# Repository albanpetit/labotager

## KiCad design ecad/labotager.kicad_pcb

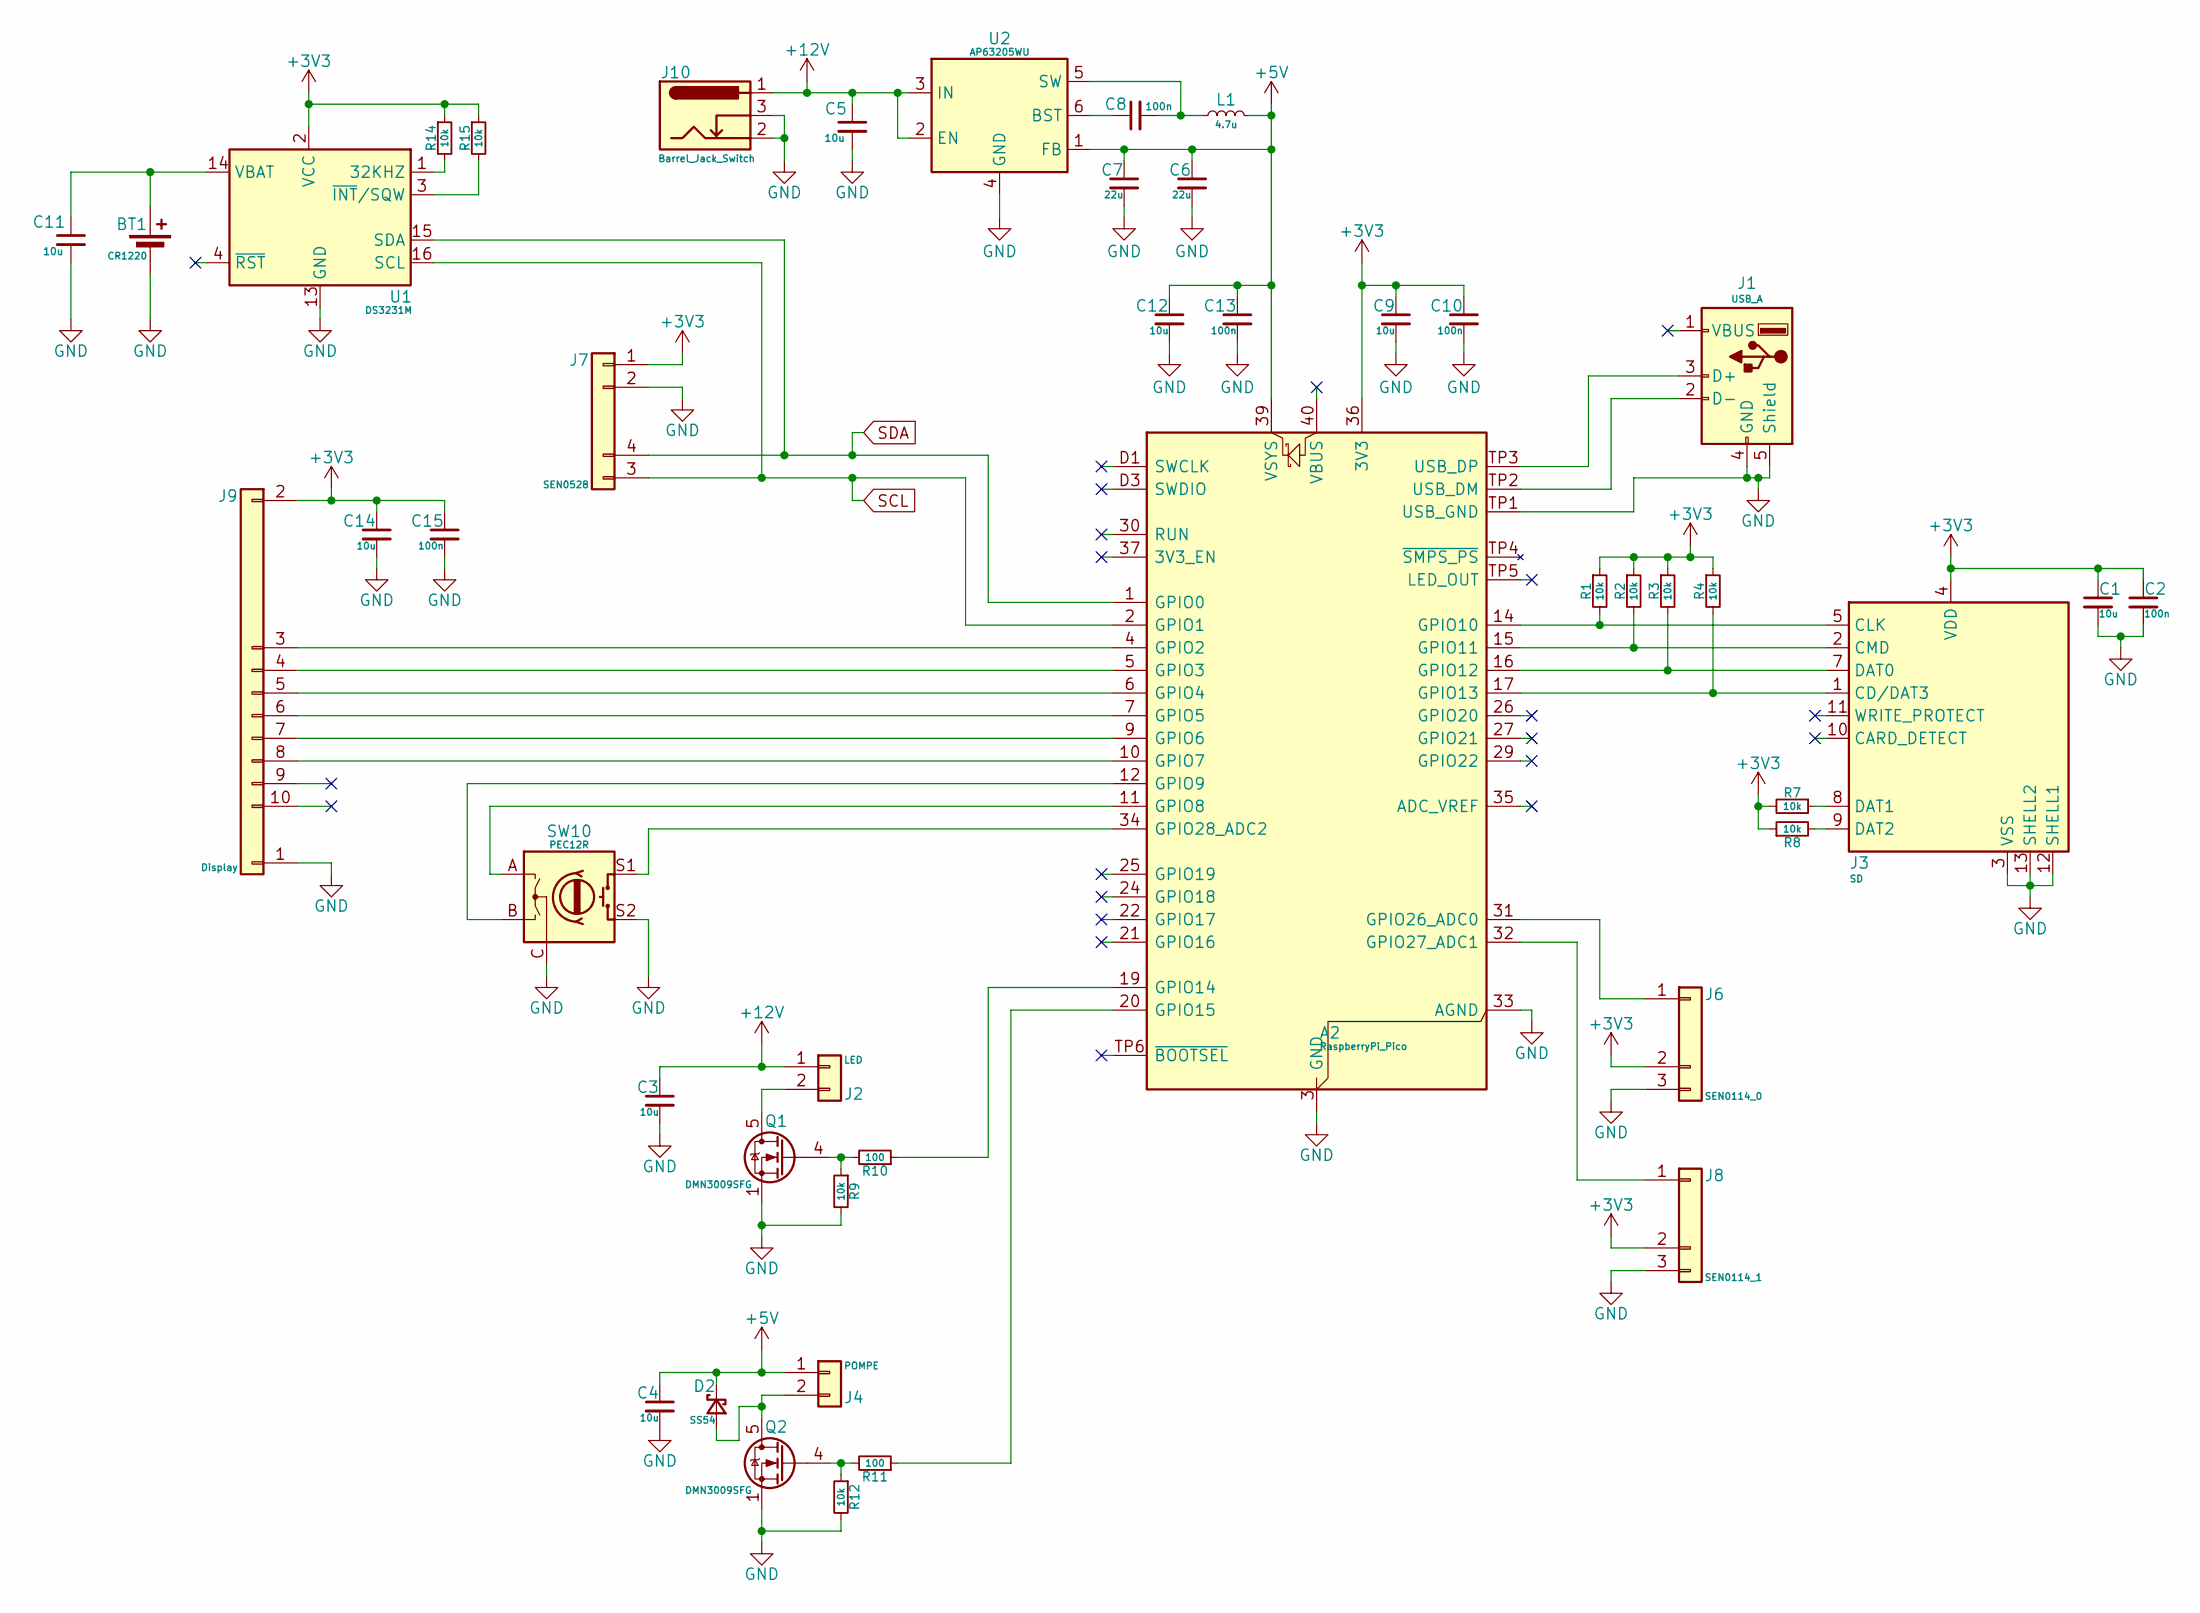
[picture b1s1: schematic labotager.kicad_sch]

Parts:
A2: RaspberryPi_Pico; RaspberryPi_Pico_SMD
BT1: CR1220; BatteryHolder_LINX_BAT-HLD-012-SMT
C1, C3, C4, C5, C9, C11, C12, C14: 10u; C_0603_1608Metric
C2, C8, C10, C13, C15: 100n; C_0603_1608Metric
C6, C7: 22u; C_0805_2012Metric
D2: SS54; D_SMA
J1: USB_A; USB3_A_Receptacle_Wuerth_692122030100
J2: LED; TerminalBlock_Phoenix_MKDS-1,5-2_1x02_P5.00mm_Horizontal
J3: SD; SD_Hirose_DM1AA_SF_PEJ82
J4: POMPE; TerminalBlock_Phoenix_MKDS-1,5-2_1x02_P5.00mm_Horizontal
J6: SEN0114_0; JST_PH_B3B-PH-SM4-TB_1x03-1MP_P2.00mm_Vertical
J7: SEN0528; JST_PH_B4B-PH-SM4-TB_1x04-1MP_P2.00mm_Vertical
J8: SEN0114_1; JST_PH_B3B-PH-SM4-TB_1x03-1MP_P2.00mm_Vertical
J9: Display; PinHeader_1x10_P2.54mm_Vertical
J10: Barrel_Jack_Switch; BarrelJack_Wuerth_694106106102_2.0x5.5mm
L1: 4.7u; L_Wuerth_MAPI-3015
Q1, Q2: DMN3009SFG; Diodes_PowerDI3333-8
R1, R2, R3, R4, R7, R8, R9, R12, R14, R15: 10k; R_0603_1608Metric
R10, R11: 100; R_0603_1608Metric
SW10: PEC12R; RotaryEncoder_Bourns_Vertical_PEC12R-3x17F-Sxxxx
U1: DS3231M; SOIC-16W_7.5x10.3mm_P1.27mm
U2: AP63205WU; TSOT-23-6

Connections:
+3V3: A2.36 (3V3), C1.1, C2.1, C9.1, C10.1, C14.1, C15.1, J3.4 (VDD), J6.2, J7.1, J8.2, J9.2, R1.1, R2.1, R3.1, R4.1, R7.2, R8.1, R14.1, R15.1, U1.2 (VCC)
+5V: A2.39 (VSYS), C4.1, C6.1, C7.1, C12.1, C13.1, D2.1 (K), J4.1, L1.2, U2.1 (FB)
+12V: C3.1, C5.1, J2.1, J10.1, U2.2 (EN), U2.3 (IN)
GND: A2.3 (GND), A2.8 (GND), A2.13 (GND), A2.18 (GND), A2.23 (GND), A2.28 (GND), A2.33 (AGND), A2.38 (GND), A2.D2 (GND), A2.TP1 (USB_GND), BT1.2 (-), C1.2, C2.2, C3.2, C4.2, C5.2, C6.2, C7.2, C9.2, C10.2, C11.2, C12.2, C13.2, C14.2, C15.2, J1.4 (GND), J1.5 (Shield), J3.3 (VSS), J3.6 (VSS), J3.12 (SHELL1), J3.13 (SHELL2), J6.3, J7.2, J8.3, J9.1, J10.2, J10.3, Q1.1 (S), Q1.2 (S), Q1.3 (S), Q2.1 (S), Q2.2 (S), Q2.3 (S), R9.2, R12.2, SW10.C, SW10.S2, U1.5 (GND), U1.6 (GND), U1.7 (GND), U1.8 (GND), U1.9 (GND), U1.10 (GND), U1.11 (GND), U1.12 (GND), U1.13 (GND), U2.4 (GND)
unnamed: A2.4 (GPIO2), J9.3
unnamed: A2.5 (GPIO3), J9.4
unnamed: A2.6 (GPIO4), J9.5
unnamed: A2.7 (GPIO5), J9.6
unnamed: A2.9 (GPIO6), J9.7
unnamed: A2.10 (GPIO7), J9.8
unnamed: A2.11 (GPIO8), SW10.A
unnamed: A2.12 (GPIO9), SW10.B
unnamed: A2.14 (GPIO10), J3.5 (CLK), R1.2
unnamed: A2.15 (GPIO11), J3.2 (CMD), R2.2
unnamed: A2.16 (GPIO12), J3.7 (DAT0), R3.2
unnamed: A2.17 (GPIO13), J3.1 (CD/DAT3), R4.2
unnamed: A2.19 (GPIO14), R10.1
unnamed: A2.20 (GPIO15), R11.1
unnamed: A2.31 (GPIO26_ADC0), J6.1
unnamed: A2.32 (GPIO27_ADC1), J8.1
unnamed: A2.34 (GPIO28_ADC2), SW10.S1
unnamed: A2.TP2 (USB_DM), J1.2 (D-)
unnamed: A2.TP3 (USB_DP), J1.3 (D+)
unnamed: BT1.1 (+), C11.1, U1.14 (VBAT)
unnamed: D2.2 (A), J4.2, Q2.5 (D)
unnamed: J2.2, Q1.5 (D)
unnamed: J3.8 (DAT1), R7.1
unnamed: J3.9 (DAT2), R8.2
unnamed: Q1.4 (G), R9.1, R10.2
unnamed: Q2.4 (G), R11.2, R12.1
unnamed: R14.2, U1.1 (32KHZ)
unnamed: R15.2, U1.3 (~INT/SQW)
unnamed: C8.1, U2.6 (BST)
unnamed: C8.2, L1.1, U2.5 (SW)
SCL: A2.2 (GPIO1), J7.3, U1.16 (SCL)
SDA: A2.1 (GPIO0), J7.4, U1.15 (SDA)

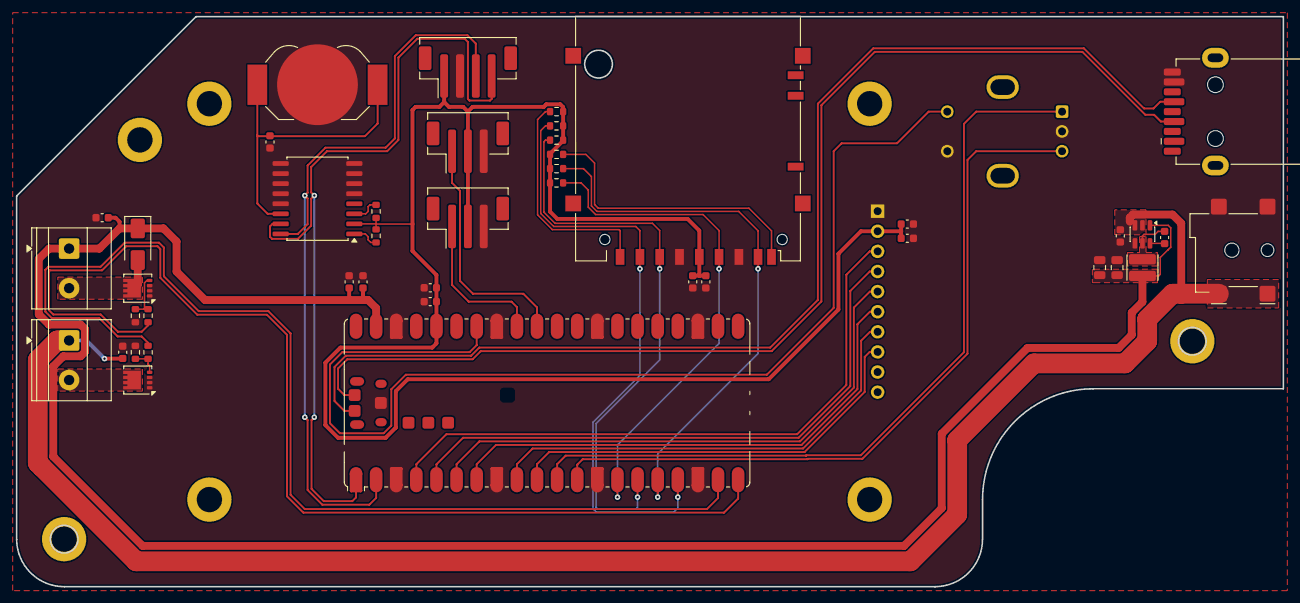
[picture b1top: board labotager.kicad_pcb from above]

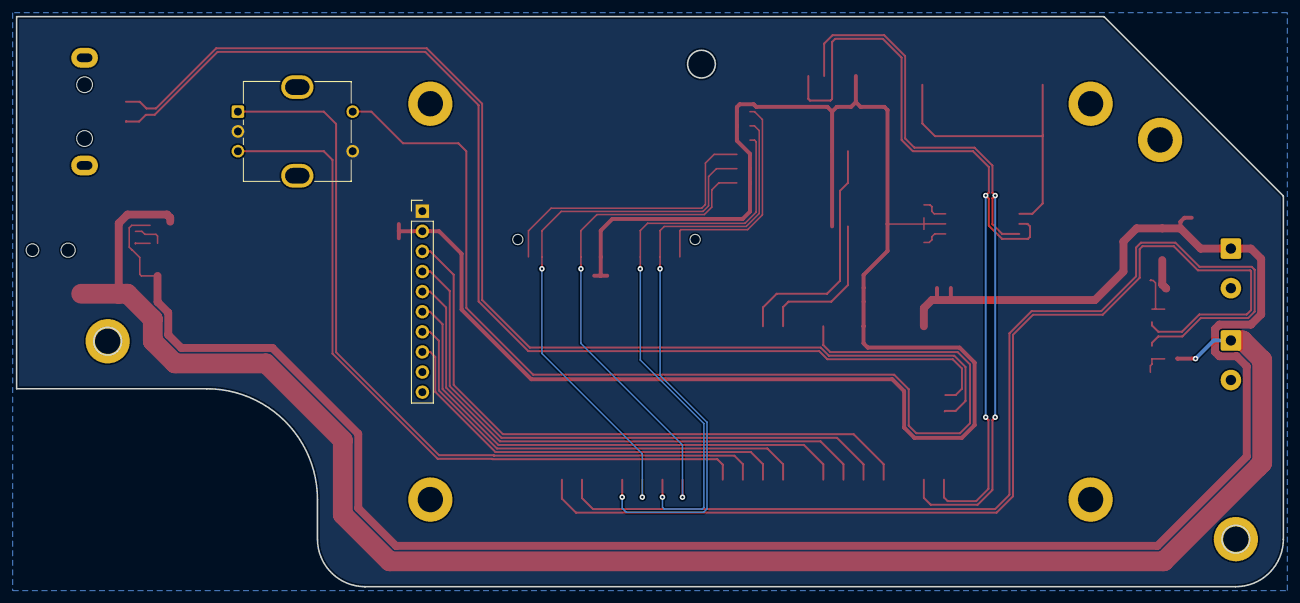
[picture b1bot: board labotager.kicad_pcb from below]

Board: 2 copper layers, 160.0 x 72.0 mm, 45 parts (2 on the bottom side), 36 nets.

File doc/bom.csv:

"Id";"Designator";"Footprint";"Quantity";"Designation";"Supplier and ref";
1;"J1";"USB3_A_Receptacle_Wuerth_692122030100";1;"USB_A";;;
2;"Q2,Q1";"Diodes_PowerDI3333-8";2;"DMN3009SFG";;;
3;"C3,C4,C9,C14,C12,C5,C1,C11";"C_0603_1608Metric";8;"10u";;;
4;"R11,R10";"R_0603_1608Metric";2;"100";;;
5;"R2,R7,R8,R9,R14,R15,R12,R3,R4,R1";"R_0603_1608Metric";10;"10k";;;
6;"C13,C8,C15,C2,C10";"C_0603_1608Metric";5;"100n";;;
7;"A2";"RaspberryPi_Pico_SMD";1;"RaspberryPi_Pico";;;
8;"C7,C6";"C_0805_2012Metric";2;"22u";;;
9;"J2";"TerminalBlock_Phoenix_MKDS-1,5-2_1x02_P5.00mm_Horizontal";1;"LED";;;
10;"J7";"JST_PH_B4B-PH-SM4-TB_1x04-1MP_P2.00mm_Vertical";1;"SEN0528";;;
11;"SW10";"RotaryEncoder_Bourns_Vertical_PEC12R-3x17F-Sxxxx";1;"PEC12R";;;
12;"BT1";"BatteryHolder_LINX_BAT-HLD-012-SMT";1;"CR1220";;;
13;"J4";"TerminalBlock_Phoenix_MKDS-1,5-2_1x02_P5.00mm_Horizontal";1;"POMPE";;;
14;"L1";"L_Wuerth_MAPI-3015";1;"4.7u";;;
15;"D2";"D_SMA";1;"SS54";;;
16;"J10";"BarrelJack_Wuerth_694106106102_2.0x5.5mm";1;"Barrel_Jack_Switch";;;
17;"U2";"TSOT-23-6";1;"AP63205WU";;;
18;"J6";"JST_PH_B3B-PH-SM4-TB_1x03-1MP_P2.00mm_Vertical";1;"SEN0114_0";;;
19;"J3";"SD_Hirose_DM1AA_SF_PEJ82";1;"SD";;;
20;"U1";"SOIC-16W_7.5x10.3mm_P1.27mm";1;"DS3231M";;;
21;"J8";"JST_PH_B3B-PH-SM4-TB_1x03-1MP_P2.00mm_Vertical";1;"SEN0114_1";;;
22;"J9";"PinHeader_1x10_P2.54mm_Vertical";1;"Display";;;

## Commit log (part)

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2026-04-15 chore: untrack .history, add to .gitignore
2026-04-15 chore: remove .history submodule, add to .gitignore
2026-04-15 chore: untrack media alias, add to .gitignore
2026-04-15 fix(fw): change the way to exit params edition for a long press
2026-04-15 fix(fw): change params format for date, h:m
2026-04-15 fix(fw): change params date format to j:m:y
2026-04-15 fix(fw): change light logic, start hour and end hour
2026-04-15 feat(fw): add 2 editable parameter for max temp and min temp
2026-04-15 feat(fw): change pump logic to trigger on light up hours
2026-04-15 fix(fw): change grow counter setup to fix a start date
2026-04-15 fix(fw): fix screen backlight flag to prevent noise on startup
2026-04-15 fix(fw): fix some bugs
2026-04-15 fix(fw): fix some errors if light up hour is equal to light off
2026-04-15 fix(fw): fix some sd card error
2026-04-16 fix(fw): fix error with screen on startup
2026-04-16 refactor(fw): refactor readness of the code, rename some var rebind const
2026-04-16 refactor(fw): improve firmware maintainability
    - Sanitize all config.txt values after loading (settings_sanitize):
    clamps hours, temps, thresholds to valid ranges, guards against
    corrupt or hand-edited config producing invalid runtime state
    - Remove last_log_millis from SensorData — it was logger-internal
    scheduling state leaking into the shared struct; now a static local
    in logger_update()
2026-04-16 refactor(fw): factorize repeated patterns
    - Add minutes_since_midnight(h, m) helper in config.h — replaces the
    inline h*60+m expression duplicated in lighting.cpp (×3) and
    display.cpp apply_delta
    - Extract commit_staged_rtc() in display.cpp — the RTC apply block
    was copy-pasted verbatim in MODE_PARAM_SELECT and MODE_PARAM_EDIT
    LONG_PRESS handlers
2026-04-20 refactor(fw): name all remaining magic literals
    - Add timing constants where bare literals remained:
    SOIL_READ_INTERVAL_MS (500), AHT20_INIT_SETTLE_MS (10),
    AHT20_FRAME_BYTES (6) → sensors.cpp
    RTC_READ_INTERVAL_MS (1000) → rtc_mgr.cpp
    SD_RETRY_INTERVAL_MS (5000), SD_HEALTH_INTERVAL_MS (10000)
    → logger.cpp
2026-04-20 refactor(fw): improve maintainability
    - Extract settings_apply_defaults() in logger.h/cpp — centralizes the
    compile-time defaults so adding a new setting only requires updating
    state.h, config.h, and the helper (not also main.cpp setup())
    - Replace raw sw_state integers 0-4 with enum SwState in encoder.cpp
    (SW_IDLE, SW_DEBOUNCE_PRESS, SW_HELD, SW_DEBOUNCE_RELEASE,
    SW_LONG_EMITTED) — state machine is now self-documenting
2026-04-20 refactor(fw): eliminate duplicated logic
    - Extract scroll_update(cursor, scroll, ev, max, shown) → ScrollResult
    in display.cpp — the cursor+scroll arithmetic was duplicated verbatim
    in MODE_DETAILS_SCROLL and MODE_PARAM_SELECT; both now call the helper
    and branch on SCROLL_UNCHANGED / SCROLL_SAME_WINDOW / SCROLL_WINDOW_SHIFTED
    - Extract handle_hw_diag(displayed, error, render_fn, ev) in display.cpp
    — the AHT20 and RTC diagnostic screen blocks were structurally identical;
2026-04-20 refactor(fw): improve readability, maintainability, and reduce duplication
    display.cpp
    - Add LIST_TEXT_X_LEFT/RIGHT/Y_OFFSET constants — removes 50/265/13 magic
    numbers shared between render_details_row and render_param_row
    - Add PARAM_YEAR_MIN/MAX (2024/2069) — year bounds now named, no longer
    duplicated across PARAM_DATE and PARAM_GROW_START branches
    - Add HW_ERROR_MSG_Y/HINT_Y — aligns render_sd_error y position with the
2026-04-20 refactor(fw): fix last audit points in display.cpp
    - Rename y → yr in render_param_row: eliminates variable shadowing of the
    outer item-position `y`, removes compiler warning
    - Fix Settings section comment: "10 items total" → "8 items total"
    - Rename HOME_REFRESH_MS → LIVE_REFRESH_MS and update its comment: the
    constant governs both Home (partial update) and Details (full redraw),
    the old name implied Home only
2026-04-21 refactor(fw): fix last audit points in display.cpp and config.h
    display.cpp
    - Fix render_home_update comment: the function is called both from
    render_home() on full render and directly by the periodic timer
    (LIVE_REFRESH_MS) for partial updates; the old comment implied
    timer-only
    - Init h = 0, m = 0 in render_param_row: removes -Wmaybe-uninitialized
2026-04-21 feat(fw): refresh Details sensor values at 1 Hz without flicker
    Add DETAILS_REFRESH_MS (1000 ms) and last_details_refresh_ms, independent
    from the Home timer (LIVE_REFRESH_MS = 60 s).
    Every second, each visible Details row is redrawn via render_details_row()
    directly — the item background image covers stale text pixels and fresh
    values are painted on top. The global background and title are never
    touched, avoiding the repaint flash that a full do_render pass would cause.
2026-04-21 feat(fw): redesign CSV log format with ID, grow day, and lighting duration
    - New header: id, date, heure, jour_croissance, temp_air_c,
    hum_air_pct, hum_sol_pct, duree_eclairage_min
    - id: auto-incrementing uint32_t; count_log_rows() reads the existing
    file at boot so IDs continue across reboots without persisting state
    - date: DD/MM/YYYY; heure: HH:MM:SS (separate columns, more spreadsheet-
    friendly than the former ISO-8601 datetime)
2026-04-21 fix(fw): change interval of csv export
2026-04-29 fix(fw): pin SdFat to exact version 2.2.3
    SdFat versions above 2.2.3 include PIO-SDIO support for RP2040 that
    pulls in Pico SDK headers (hardware/pio.h) incompatible with the
    Arduino-Mbed framework, causing build failures on machines that resolve
    the ^2.2.3 semver range to a newer release.
2026-04-29 docs(tools): add Windows PowerShell instructions to tools/README.md
    Add setup and usage commands for Windows alongside the existing macOS/Linux
    section, including the PowerShell execution policy workaround and the
    Get-Item glob syntax required on Windows.
2026-04-29 fix(tools): expand glob patterns in png2h.py for Windows compatibility
    PowerShell does not expand wildcards for external commands, so *.png was
    passed as a literal string to Python and no files were matched. The script
    now calls glob.glob() on each input argument so wildcard expansion works
    on all platforms. Update the README Windows command accordingly.
2026-04-30 fix(doc): correct command to export all images
2026-04-30 refactor(ui): replace PNGdec runtime decoding with pre-decoded RGB565 headers
    All component images are now stored as pre-decoded RGB565 arrays generated
    by tools/png2h.py, eliminating PNGdec runtime decompression on every draw.
    png2h.py:
    - Emit `static constexpr int16_t name_W/H` aliases alongside the existing
    UPPER_CASE defines so the UI_IMG macro can use token pasting
    - Emit `static constexpr const uint8_t *name_mask = nullptr` for opaque
2026-05-02 feat(pump): add max watering duration and inter-cycle cooldown
    Watering cycles are now bounded in time and separated by a configurable
    cooldown period to prevent overwatering.
    pump.cpp:
    - Stop the pump after watering_duration_s seconds (default 5 s) even if
    the soil threshold has not been reached yet
    - Block new cycles until watering_cooldown_min minutes have elapsed since
2026-05-02 fix(fw): change name of parameter
2026-05-02 feat(pump): add watering enable/disable toggle
    Add a boolean setting to allow watering to be suspended without changing
    the other watering parameters.
    config.h: add DEFAULT_WATERING_ENABLED (1)
    state.h: add watering_enabled field to Settings
    pump.cpp: gate cycle start on settings.watering_enabled
    logger.cpp: apply default, sanitize, load and save watering_enabled
2026-05-02 feat(display): add configurable screen auto-sleep on encoder inactivity
    After a configurable inactivity period the backlight is cut to save energy
    and avoid light emission. Any encoder event wakes the screen without
    processing the triggering event (prevents accidental navigation).
    config.h: add DEFAULT_SLEEP_ENABLED (1) and DEFAULT_SLEEP_TIMEOUT_MIN (5)
    state.h: add sleep_enabled and sleep_timeout_min fields to Settings
    logger.cpp: apply defaults, sanitize (1–59 min), load and save under keys
2026-06-18 fix(sensors): recalibrate soil moisture wet-point to match measured ADC value
    SOIL_WET_VAL was set to 800 but a fully-soaked sample read 71% instead of
    100%, indicating the actual ADC value at saturation is closer to 1583.
2026-06-18 fix(storage): parse owner_name before numeric validation in config loader
    Every config line was first run through strtol() to validate it as a
    number; owner_name is a text value, so it never contained leading digits
    and was silently dropped before reaching its dedicated handler. As a
    result, editing owner_name on the SD card had no effect after reload.
2026-06-18 fix(sensors): oversample soil moisture ADC to reject noise spikes
    A single noisy analogRead() sample could momentarily drop soil_pct below
    the watering threshold and trigger the pump even with fully soaked soil,
    since pump_update() reacts to each reading with no debounce. Average 8
    samples per reading cycle to smooth out ADC noise.
2026-06-18 fix(storage): harden SD writes against power-loss corruption
    Random parameter resets and unreadable single-letter folders ("N", "M")
    on the SD card pointed to FAT corruption from power loss mid-write.
    - sync() before close() on every critical SD write (log creation, CSV
    rows, config save) to shrink the corruption window.
    - Parse config.txt into a scratch copy and only commit it if a
    config_version sentinel line is present and valid, instead of
2026-06-18 fix(storage): archive log.csv when its header no longer matches the firmware
    A log.csv created by an older firmware version (different columns) kept
    its original header forever, since it's only written when the file is
    first created. New rows from a later firmware version were appended
    underneath that stale header, producing a CSV where data didn't line
    up with column names.
    ensure_log_structure() now checks the existing header against the one
